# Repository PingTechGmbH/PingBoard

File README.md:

# PingBoard

> Mini keyboard with just four keys for core macros.

## Building the firmware

### with Platform.io

Install platformio with

```bash
pip3 install platformio
```

Or pick any other installation method from https://docs.platformio.org/en/latest/core/installation.html

Review https://docs.platformio.org/en/latest//faq.html#platformio-udev-rules and install the udev rules.

To refresh your groups inside a running session without logging in, you can use:

```bash
su - $USER
```

After doing this (or a reboot), you can then flash the firmware with:

```bash
cd Prototype/PlatformioProjekt
platformio run -t upload
```

## License

This project is published under the MIT license, see [LICENSE](LICENSE.txt) for details.

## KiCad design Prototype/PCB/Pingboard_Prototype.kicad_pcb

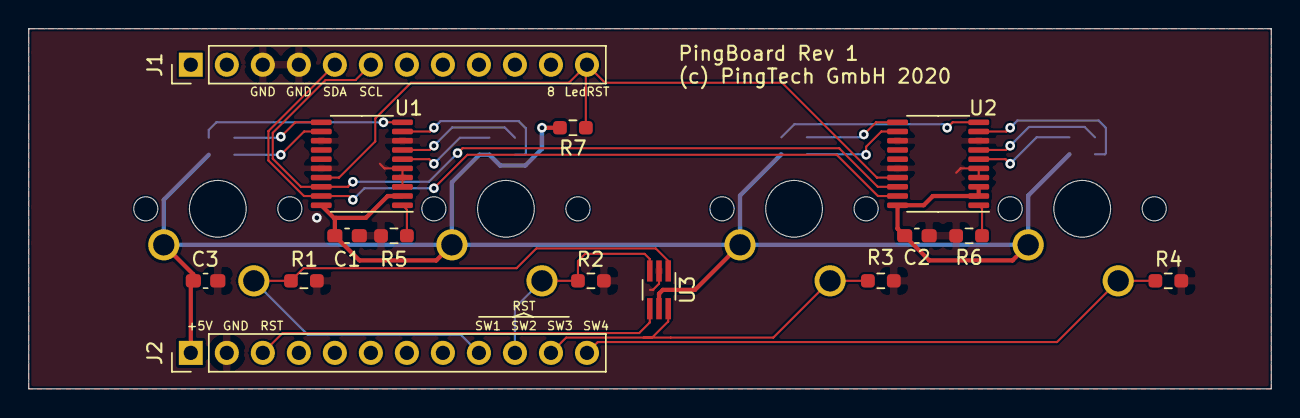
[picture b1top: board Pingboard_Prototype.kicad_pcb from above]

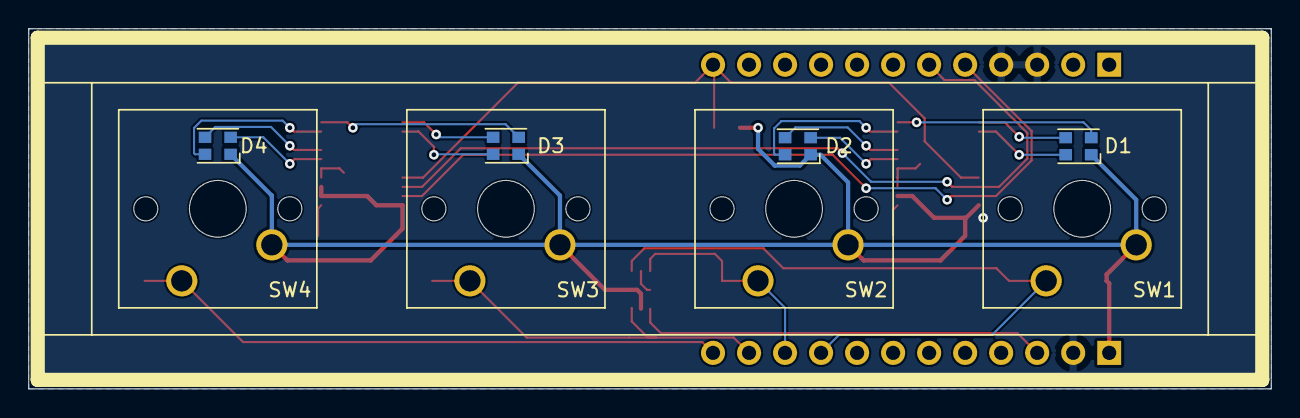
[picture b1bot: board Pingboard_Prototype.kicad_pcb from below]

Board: 2 copper layers, 87.6 x 25.4 mm, 23 parts (8 on the bottom side), 24 nets.

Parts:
C1, C2: 100n; C_0603_1608Metric_Pad1.08x0.95mm_HandSolder
C3: 1u; C_0603_1608Metric_Pad1.08x0.95mm_HandSolder
D1, D2, D3, D4: LED_ARGB; LED_ASMB-KTF0-0A306
J1, J2: Conn_01x12; PinHeader_1x12_P2.54mm_Vertical
R1, R2, R3, R4, R7: 4k7; R_0603_1608Metric_Pad0.98x0.95mm_HandSolder
R5, R6: 520; R_0603_1608Metric_Pad0.98x0.95mm_HandSolder
SW1, SW2, SW3, SW4: SW_Push; SW_Cherry_MX_1.00u_PCB
U1, U2: TLC59108xPW; TSSOP-20_4.4x6.5mm_P0.65mm
U3: 74LVC1G10; SOT-363_SC-70-6_Handsoldering

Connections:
GND: C1.2, C2.2, C3.2, J1.3, J1.4, J2.2, R1.1, R2.1, R3.1, R4.1, R5.2, R6.2, U1.3, U1.4, U1.5, U1.8, U1.13, U1.16, U2.4, U2.5, U2.8, U2.13, U2.16, U3.2
LedRST: J1.12, R7.1, U1.17, U2.17
unnamed: D1.2, U1.10
unnamed: D1.3, U1.11
unnamed: D1.4, U1.12
unnamed: D2.2, U1.6
unnamed: D2.3, U1.7
unnamed: D2.4, U1.9
unnamed: D3.2, U2.10
unnamed: D3.3, U2.11
unnamed: D3.4, U2.12
unnamed: D4.2, U2.6
unnamed: D4.3, U2.7
unnamed: D4.4, U2.9
unnamed: R5.1, U1.1
unnamed: R6.1, U2.1
RST: J2.3, U3.4
SCL: J1.6, U1.18, U2.18
SDA: J1.5, U1.19, U2.19
Switch1: J2.9, R1.2, SW1.1, U3.1
Switch2: J2.10, R2.2, SW2.1, U3.3
Switch3: J2.11, R3.2, SW3.1, U3.6
Switch4: J2.12, R4.2, SW4.1
VCC: C1.1, C2.1, C3.1, D1.1, D2.1, D3.1, D4.1, J2.1, R7.2, SW1.2, SW2.2, SW3.2, SW4.2, U1.2, U1.20, U2.2, U2.3, U2.20, U3.5

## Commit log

2020-11-16 Draft 3
2020-11-16 Add library cache
2020-11-16 Draft 1
2020-11-16 Draft 4
    Arduino Huckepack
2020-11-16 Set Rext for LED current based on datasheet
    Using default values, Rext for 20 mA is 600 Ohm. We're using 520 Ohm
    for a safety margin.
2020-11-16 Prototyp PCB Rev 1
2020-11-16 Connect LED Driver reset to uC
2020-11-16 Add gitignore for Kicad projects
2020-11-16 Draft 2
2020-11-16 Draft 5
2020-12-21 Add first draft for arduino sketch
2020-12-21 Simple tool to set keyboard colors
2021-03-19 CAD und STL-Dateien des Gehäuses hinzugefügt OnShape-Link: https://cad.onshape.com/documents/afa9d689952d1619d7309606/w/a36d419d401c7f135a8c8904/e/194e84c7284c1a2dfec4041b
2021-03-22 fix connection of REXT
2021-03-23 Flip C1 and C2 to make a better VCC-GND loop
2021-04-07 move to platformio project
2021-04-13 Add documentation to Readme
2021-04-16 Add InputDebounce library dependency
2021-04-19 Increase debounce delay to 50ms
2021-04-19 Use InputDebounce library for debouncing
    https://platformio.org/lib/show/123/InputDebounce
2021-04-22 Fix name clash for SERIAL_BUFFER_SIZE
2021-04-22 Document the new serial communication format
2021-04-22 Move checkSerial closer to serial console code
2021-04-23 Clarify end-of-string marking
2021-04-23 Change color setting to COL command
2021-04-23 Adapt color-setter to new command format
2021-05-14 Implement Dimming
2021-06-07 Add Blink function
2021-06-07 Add test scripts
2021-06-07 Change blink script to not require color for OFF command
2021-06-07 Update dim script to fix args error message
2021-06-07 flush serial channel to increase reliabiliy
2021-08-06 document flashing procedure including environment setup
2022-04-04 Change project description
2022-04-04 Fix README structure
2022-04-04 Add LICENSE
2022-04-04 Add prototype picture
2022-04-04 Link picture in README
2022-07-07 Add KiCAD project files in new format
2022-07-07 Remove obsolete KiCAD files
2022-07-07 Add new local and backup files to .gitignore
2022-08-31 Add an LED test pattern on device boot
    This allows to see if LEDs are missing.
2022-08-31 Fix missing reset pin argument for led2 setup
2023-01-17 :heavy_plus_sign: Install TLC59108 library via platformio
2023-01-17 :bug: Fix that second LED controller did not work
